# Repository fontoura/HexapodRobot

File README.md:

Greetings!

This repo contains files of the Capstone Project we presented in order to get our Computer Engineering degrees, back in 2013. The project was published in Portuguese language only, but the university demanded we include an 'abstract' section written in Engish. The abstract section as published is at the end of this file. If you are an English speaker and gets interested in this project, feel free to contact us!

Our monograph (in Portuguese) can be found at: <http://repositorio.roca.utfpr.edu.br/jspui/handle/1/954>.

There is a small difference between the firmware version in this repo and the one we presented back in 2013: the version in this repo uses FreeRTOS instead of µC/OS-II for RTOS. We changed the operating system in order to avoid licensing problems.

The files are organized as follows:

./Driver - Eclipse projects with the driger and the UI's for PC and Android.

./HexapodHW - Quartus project with the reconfigurable hardware and firmware.

./PCI - Printed circuit board (in Portuguese: 'placa de circuito impresso'/'PCI') for Eagle.

Best regards.

Felipe Michels Fontoura, Leandro Piekarski do Nascimento, Lucas Longen Gioppo

--------------------------------------------------

FONTOURA, Felipe Michels; GIOPPO, Lucas Longen; DO NASCIMENTO, Leandro Piekarski. Robô Hexápode Controlado por FPGA (Hexapod Robot Controlled by FPGA). 2013. Monograph (Undergraduate) – Computer Engineering Course, UTFPR, Curitiba, Brazil.

Hexapod robots are commonly used as platform for studies on robotics, hence it is of academic interest to develop such kind of robot with open specifications. The main goal ot this project is the development of a hexapod robot controlled by FPGA, receiving highlevel commands from a computer. The development follows a spiral model in three stages: project, development and tests. Many studies were necessary in order to make the project possible, especially those regarding inverse kinematics. The project itself is divided in six parts: robot mechanics, motor electronics, robot control hardware, firmware, driver and user interface software. The robot is based on a MSR-H01 mechanical structure developed by Micromagic Systems which requires three motors per leg. There are six Corona DS329MG motors on the shoulders, and twelve BMS-620MG on other joints, all supplied by an ATX power source (140W at 5V) and optically isolated from remaining hardware. The robot control hardware includes the FPGA and its peripherals such as optocouplers, magnetometer (HMC5883), accelerometer (ADXL345) and the XBee device. The FPGA generates the control signals for the servos and other devices while embedding a NIOS II processor with 32-bit RISC architecture, capable of performances up to 250 DMIPS. The firmware was developed in C++ and is responsible for reading the sensors, sending control signals to the servos and connecting to the driver, developed in Java, through the XBee channel. The user interface software allows the user to send commands to the robot through the driver and displays readings from the sensors. The result was a robot capable of moving using a combination of inverse kinematics and other technologies. Technologically, the project has the quality of being extensible, as the FPGA allows hardware reprogramming and the software is split into individual modules. Socioeconomically, the flexibility of the robot allows using it for both teaching and research. It is also remarkable that its specification is open and so more robots like this one can be made with little effort.

Keywords: Hexapod Robot. Servomotor, Reconfigurable Logic. Object-Oriented. Spiral Method

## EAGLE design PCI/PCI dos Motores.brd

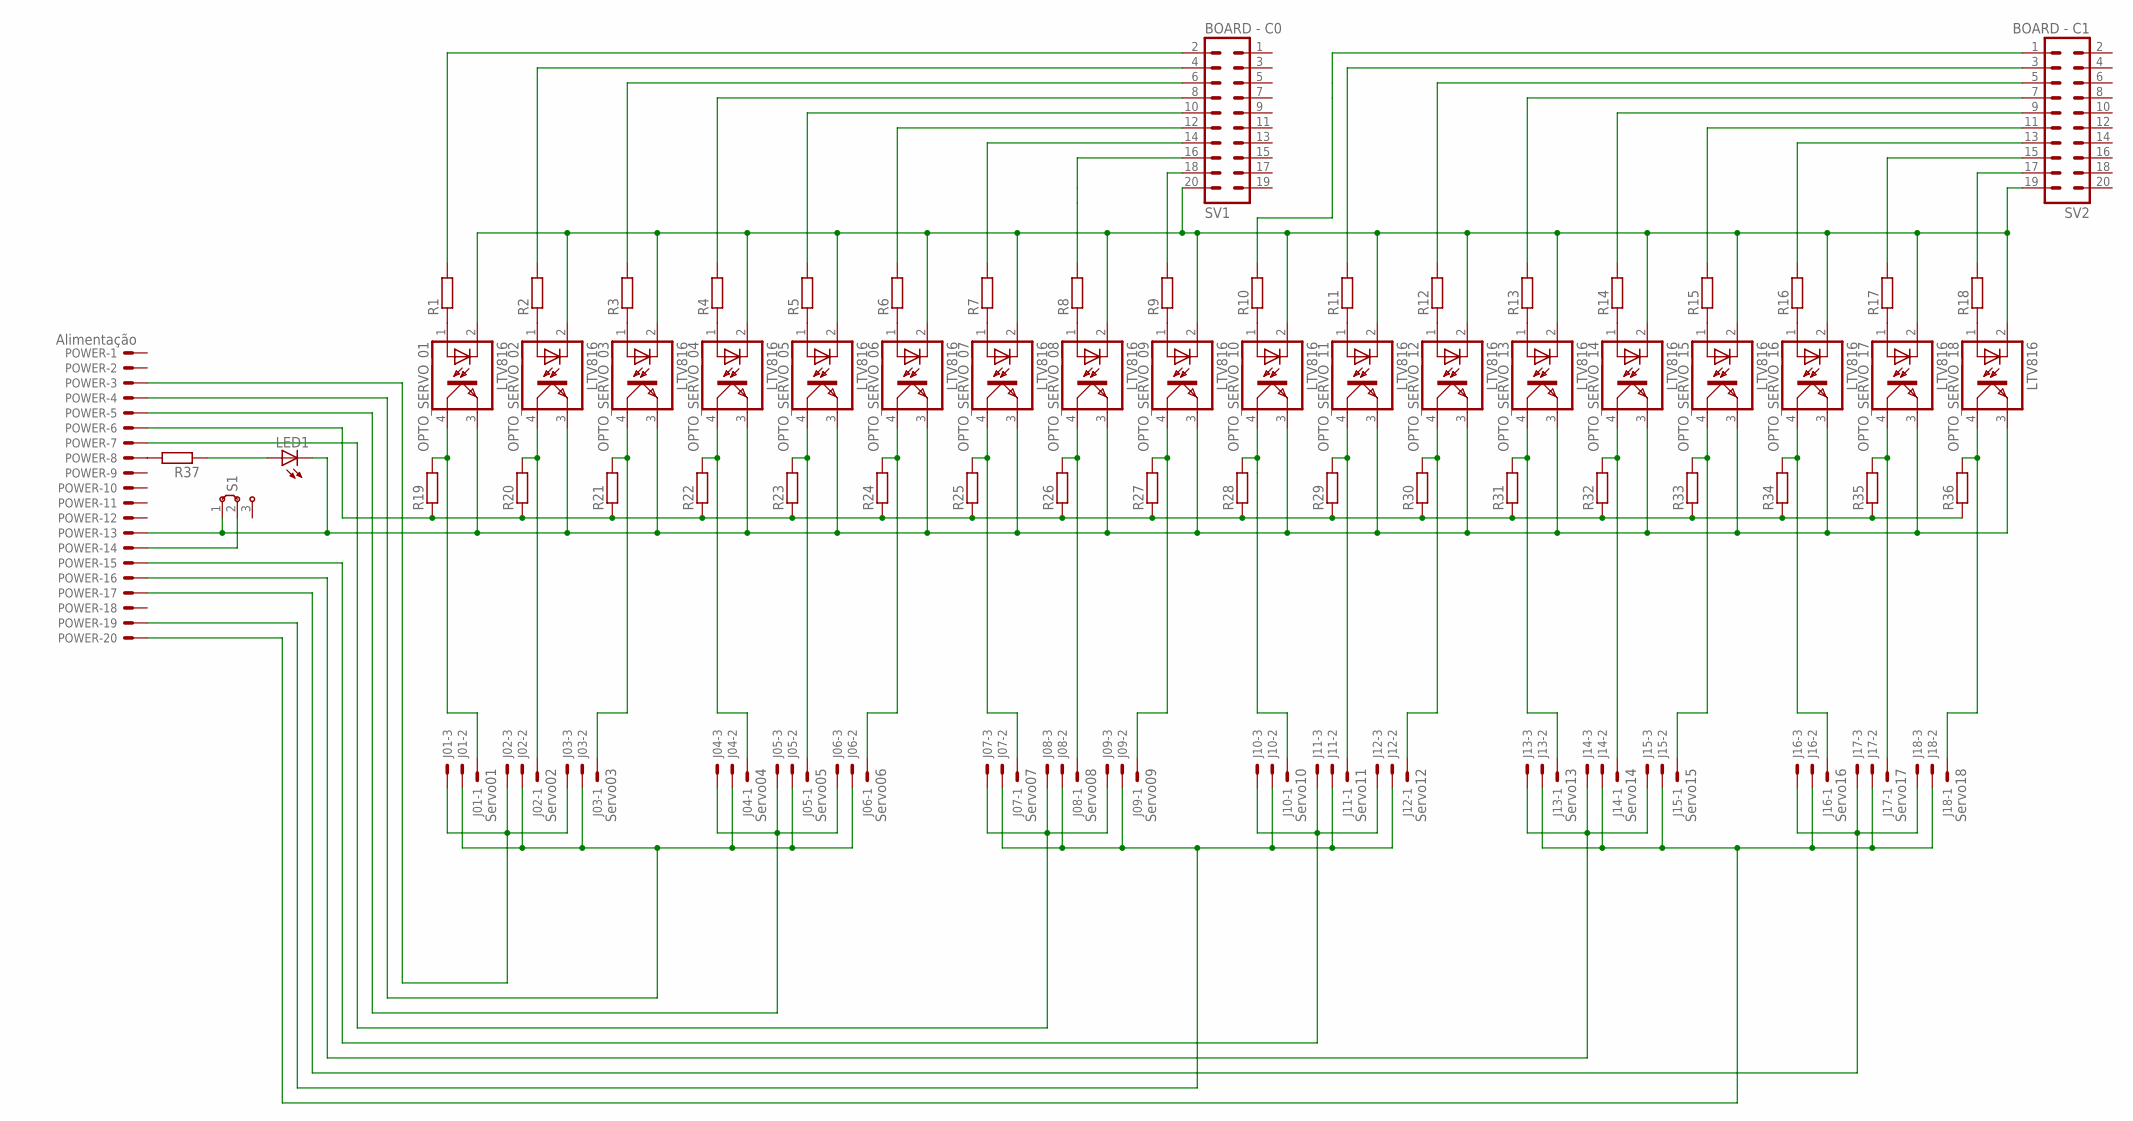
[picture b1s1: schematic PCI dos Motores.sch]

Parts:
J01: Servo01; 7395-03
J02: Servo02; 7395-03
J03: Servo03; 7395-03
J04: Servo04; 7395-03
J05: Servo05; 7395-03
J06: Servo06; 7395-03
J07: Servo07; 7395-03
J08: Servo08; 7395-03
J09: Servo09; 7395-03
J10: Servo10; 7395-03
J11: Servo11; 7395-03
J12: Servo12; 7395-03
J13: Servo13; 7395-03
J14: Servo14; 7395-03
J15: Servo15; 7395-03
J16: Servo16; 7395-03
J17: Servo17; 7395-03
J18: Servo18; 7395-03
LED1: LED_ELD260; LED_LD260
OPTO_SERVO_01, OPTO_SERVO_02, OPTO_SERVO_03, OPTO_SERVO_04, OPTO_SERVO_05, OPTO_SERVO_06, OPTO_SERVO_07, OPTO_SERVO_08, OPTO_SERVO_09, OPTO_SERVO_10, OPTO_SERVO_11, OPTO_SERVO_12, OPTO_SERVO_13, OPTO_SERVO_14, OPTO_SERVO_15, OPTO_SERVO_16, OPTO_SERVO_17, OPTO_SERVO_18: LTV816; DIL04
POWER: Alimentação; 5566-20
R1, R2, R3, R4, R5, R6, R7, R8, R9, R10, R11, R12, R13, R14, R15, R16, R17, R18, R19, R20, R21, R22, R23, R24, R25, R26, R27, R28, R29, R30, R31, R32, R33, R34, R35, R36, R37: R-EU_0309/10; 0309/10
S1: J2X2MM; 04C
SV1: BOARD - C0; ML20
SV2: BOARD - C1; ML20

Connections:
unnamed: OPTO_SERVO_01.1 (A), R1.1
unnamed: OPTO_SERVO_02.1 (A), R2.1
unnamed: OPTO_SERVO_03.1 (A), R3.1
unnamed: OPTO_SERVO_04.1 (A), R4.1
unnamed: OPTO_SERVO_05.1 (A), R5.1
unnamed: OPTO_SERVO_06.1 (A), R6.1
unnamed: OPTO_SERVO_07.1 (A), R7.1
unnamed: OPTO_SERVO_08.1 (A), R8.1
unnamed: OPTO_SERVO_09.1 (A), R9.1
unnamed: J01.1, OPTO_SERVO_01.4 (COL), R19.2
unnamed: OPTO_SERVO_10.1 (A), R10.1
unnamed: OPTO_SERVO_11.1 (A), R11.1
unnamed: R18.2, SV2.17
unnamed: OPTO_SERVO_12.1 (A), R12.1
unnamed: OPTO_SERVO_13.1 (A), R13.1
unnamed: OPTO_SERVO_14.1 (A), R14.1
unnamed: OPTO_SERVO_15.1 (A), R15.1
unnamed: OPTO_SERVO_16.1 (A), R16.1
unnamed: OPTO_SERVO_17.1 (A), R17.1
unnamed: OPTO_SERVO_18.1 (A), R18.1
unnamed: J02.1, OPTO_SERVO_02.4 (COL), R20.2
unnamed: J03.1, OPTO_SERVO_03.4 (COL), R21.2
unnamed: J04.1, OPTO_SERVO_04.4 (COL), R22.2
unnamed: J05.1, OPTO_SERVO_05.4 (COL), R23.2
unnamed: J06.1, OPTO_SERVO_06.4 (COL), R24.2
unnamed: J07.1, OPTO_SERVO_07.4 (COL), R25.2
unnamed: J18.1, OPTO_SERVO_18.4 (COL), R36.2
unnamed: J08.1, OPTO_SERVO_08.4 (COL), R26.2
unnamed: J09.1, OPTO_SERVO_09.4 (COL), R27.2
unnamed: J11.1, OPTO_SERVO_11.4 (COL), R29.2
unnamed: J10.1, OPTO_SERVO_10.4 (COL), R28.2
unnamed: J12.1, OPTO_SERVO_12.4 (COL), R30.2
unnamed: POWER.6, R19.1, R20.1, R21.1, R22.1, R23.1, R24.1, R25.1, R26.1, R27.1, R28.1, R29.1, R30.1, R31.1, R32.1, R33.1, R34.1, R35.1, R36.1
unnamed: J16.1, OPTO_SERVO_16.4 (COL), R34.2
unnamed: J15.1, OPTO_SERVO_15.4 (COL), R33.2
unnamed: J14.1, OPTO_SERVO_14.4 (COL), R32.2
unnamed: J13.1, OPTO_SERVO_13.4 (COL), R31.2
unnamed: LED1.K (C), OPTO_SERVO_01.3 (EMIT), OPTO_SERVO_02.3 (EMIT), OPTO_SERVO_03.3 (EMIT), OPTO_SERVO_04.3 (EMIT), OPTO_SERVO_05.3 (EMIT), OPTO_SERVO_06.3 (EMIT), OPTO_SERVO_07.3 (EMIT), OPTO_SERVO_08.3 (EMIT), OPTO_SERVO_09.3 (EMIT), OPTO_SERVO_10.3 (EMIT), OPTO_SERVO_11.3 (EMIT), OPTO_SERVO_12.3 (EMIT), OPTO_SERVO_13.3 (EMIT), OPTO_SERVO_14.3 (EMIT), OPTO_SERVO_15.3 (EMIT), OPTO_SERVO_16.3 (EMIT), OPTO_SERVO_17.3 (EMIT), OPTO_SERVO_18.3 (EMIT), POWER.13, S1.1
unnamed: J01.2, J02.2, J03.2, J04.2, J05.2, J06.2, POWER.4
unnamed: J07.2, J08.2, J09.2, J10.2, J11.2, J12.2, POWER.19
unnamed: J13.2, J14.2, J15.2, J16.2, J17.2, J18.2, POWER.20
unnamed: J01.3, J02.3, J03.3, POWER.3
unnamed: POWER.8, R37.2
unnamed: J07.3, J08.3, J09.3, POWER.7
unnamed: J10.3, J11.3, J12.3, POWER.15
unnamed: J13.3, J14.3, J15.3, POWER.16
unnamed: J16.3, J17.3, J18.3, POWER.17
unnamed: OPTO_SERVO_01.2 (C), OPTO_SERVO_02.2 (C), OPTO_SERVO_03.2 (C), OPTO_SERVO_04.2 (C), OPTO_SERVO_05.2 (C), OPTO_SERVO_06.2 (C), OPTO_SERVO_07.2 (C), OPTO_SERVO_08.2 (C), OPTO_SERVO_09.2 (C), OPTO_SERVO_10.2 (C), OPTO_SERVO_11.2 (C), OPTO_SERVO_12.2 (C), OPTO_SERVO_13.2 (C), OPTO_SERVO_14.2 (C), OPTO_SERVO_15.2 (C), OPTO_SERVO_16.2 (C), OPTO_SERVO_17.2 (C), OPTO_SERVO_18.2 (C), SV1.20, SV2.19
unnamed: LED1.A, R37.1
unnamed: R1.2, SV1.2
unnamed: J04.3, J05.3, J06.3, POWER.5
unnamed: POWER.14, S1.2
unnamed: R2.2, SV1.4
unnamed: R9.2, SV1.18
unnamed: R8.2, SV1.16
unnamed: R7.2, SV1.14
unnamed: R6.2, SV1.12
unnamed: R5.2, SV1.10
unnamed: R4.2, SV1.8
unnamed: R3.2, SV1.6
unnamed: J17.1, OPTO_SERVO_17.4 (COL), R35.2
unnamed: R17.2, SV2.15
unnamed: R16.2, SV2.13
unnamed: R15.2, SV2.11
unnamed: R14.2, SV2.9
unnamed: R13.2, SV2.7
unnamed: R12.2, SV2.5
unnamed: R11.2, SV2.3
unnamed: R10.2, SV2.1

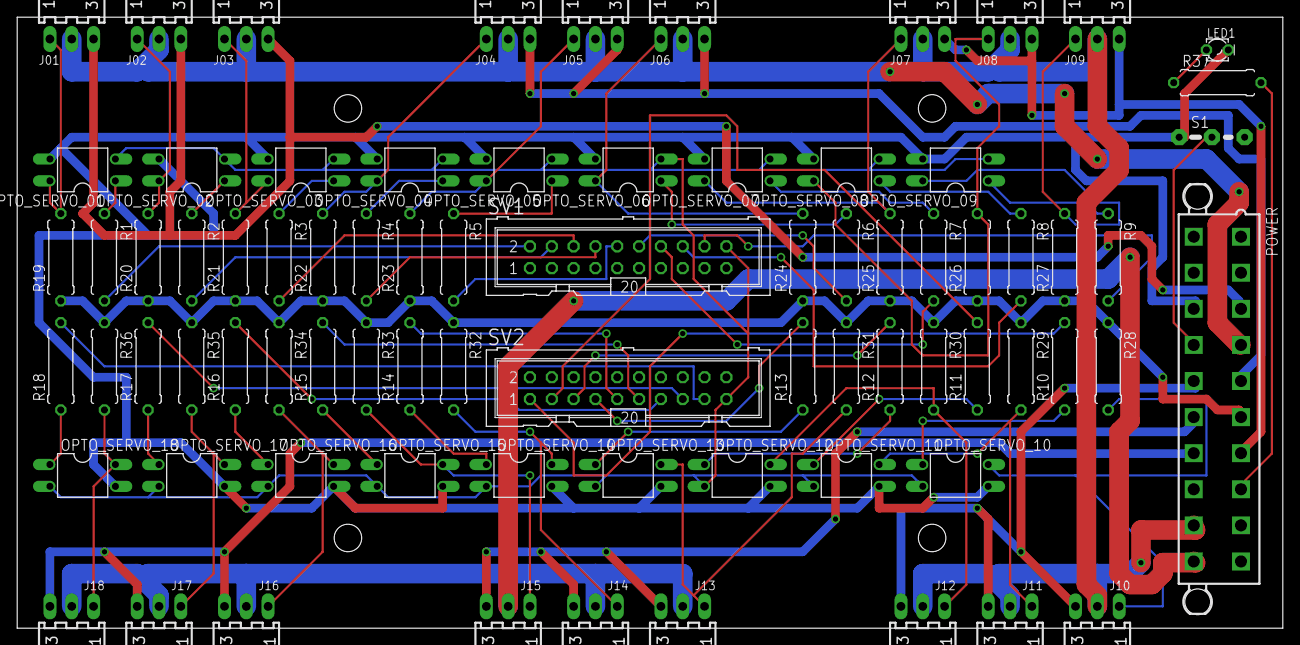
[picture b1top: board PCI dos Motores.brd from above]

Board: 2 copper layers, 147.3 x 71.1 mm, 78 parts (0 on the bottom side), 69 nets.

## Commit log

2017-07-22 Update README files.
2017-07-22 Adding driver and UI.
2017-07-22 Updating README file.
2017-07-22 Adding PCB files.
2017-07-22 Adding firmware files.
2017-07-22 Adding Quartus project.
2017-07-22 Fixing formatting of README files.
